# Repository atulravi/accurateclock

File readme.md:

All files for the accurate clock project!

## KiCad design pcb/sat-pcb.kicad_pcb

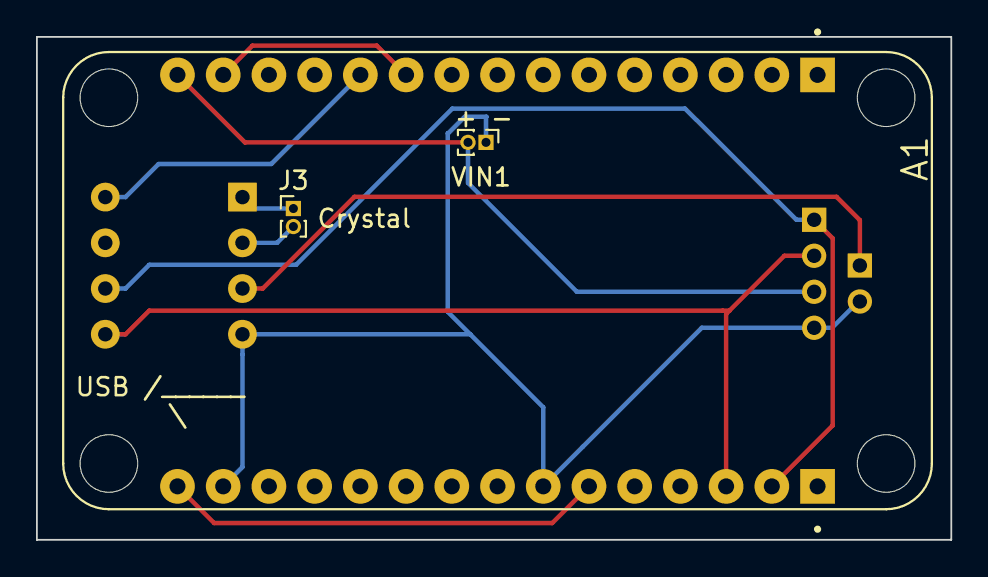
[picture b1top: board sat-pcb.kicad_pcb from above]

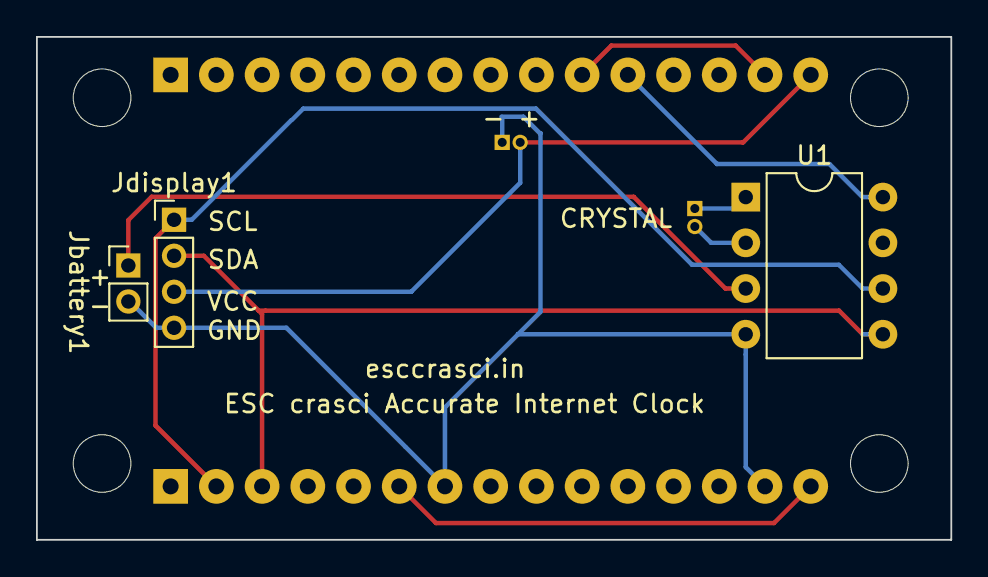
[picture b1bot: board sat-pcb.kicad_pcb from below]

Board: 2 copper layers, 50.8 x 27.9 mm, 6 parts (3 on the bottom side), 8 nets.

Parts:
A1: NODE MCU; SEEED_113990105
J3: Conn_01x02_Socket; PinHeader_1x02_P1.00mm_Vertical
Jbattery1: Conn_01x02_Socket; PinHeader_1x02_P2.00mm_Vertical
Jdisplay1: Conn_01x04_Socket; PinHeader_1x04_P2.00mm_Vertical
U1: DS1307+; DIP-8_W7.62mm
VIN1: Conn_01x02_Socket; PinHeader_1x02_P1.00mm_Vertical

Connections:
unnamed: A1.J1_11 (3V3), U1.8 (VCC)
unnamed: A1.J1_10 (GND), A1.J1_14 (GND)
unnamed: A1.J2_6 (3V3), A1.J2_15 (3V3)
unnamed: Jbattery1.1, U1.3 (VBAT)
gns: A1.J2_7 (GND), A1.J2_14 (GND), Jbattery1.2, Jdisplay1.4, U1.4 (GND), VIN1.1
scl: A1.J2_2 (D1), Jdisplay1.1, U1.6 (SCL)
sda: A1.J2_3 (D2), Jdisplay1.2, U1.5 (SDA)
vout5: A1.J1_15 (VIN), Jdisplay1.3, VIN1.2

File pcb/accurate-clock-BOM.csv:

"Id";"Designator";"Footprint";"Quantity";"Designation";"Supplier and ref";
1;"A1";"SEEED_113990105";1;"NODE MCU ";;;
2;"VIN1,J3";"PinHeader_1x02_P1.00mm_Vertical";2;"Conn_01x02_Socket";;;
3;"U1";"DIP-8_W7.62mm";1;"DS1307+";;;
4;"Jbattery1";"PinHeader_1x02_P2.00mm_Vertical";1;"Conn_01x02_Socket";;;
5;"Jdisplay1";"PinHeader_1x04_P2.00mm_Vertical";1;"Conn_01x04_Socket";;;
